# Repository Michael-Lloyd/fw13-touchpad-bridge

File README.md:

# Framework 13 Touchpad to USB bridge

Demo video can be found [here](https://youtu.be/qEcvwA03GHM?si=J2vbeN7p9iwUP8ut)

## Hardware files

You can find all of the hardware files under `hardware/` including the the gerbers, drill files and CSV that can be imported into Digikey carts. 

I've done everything in KiCAD, which is free on most systems. 

## Firmware 

The firmware is under `firmware/` and can be built using the Raspberry Pi pico-sdk toolchain. 

If you have any questions or want to talk to me about this project, you can contact me using one of the methods on my website at [micl.dev](https://micl.dev)

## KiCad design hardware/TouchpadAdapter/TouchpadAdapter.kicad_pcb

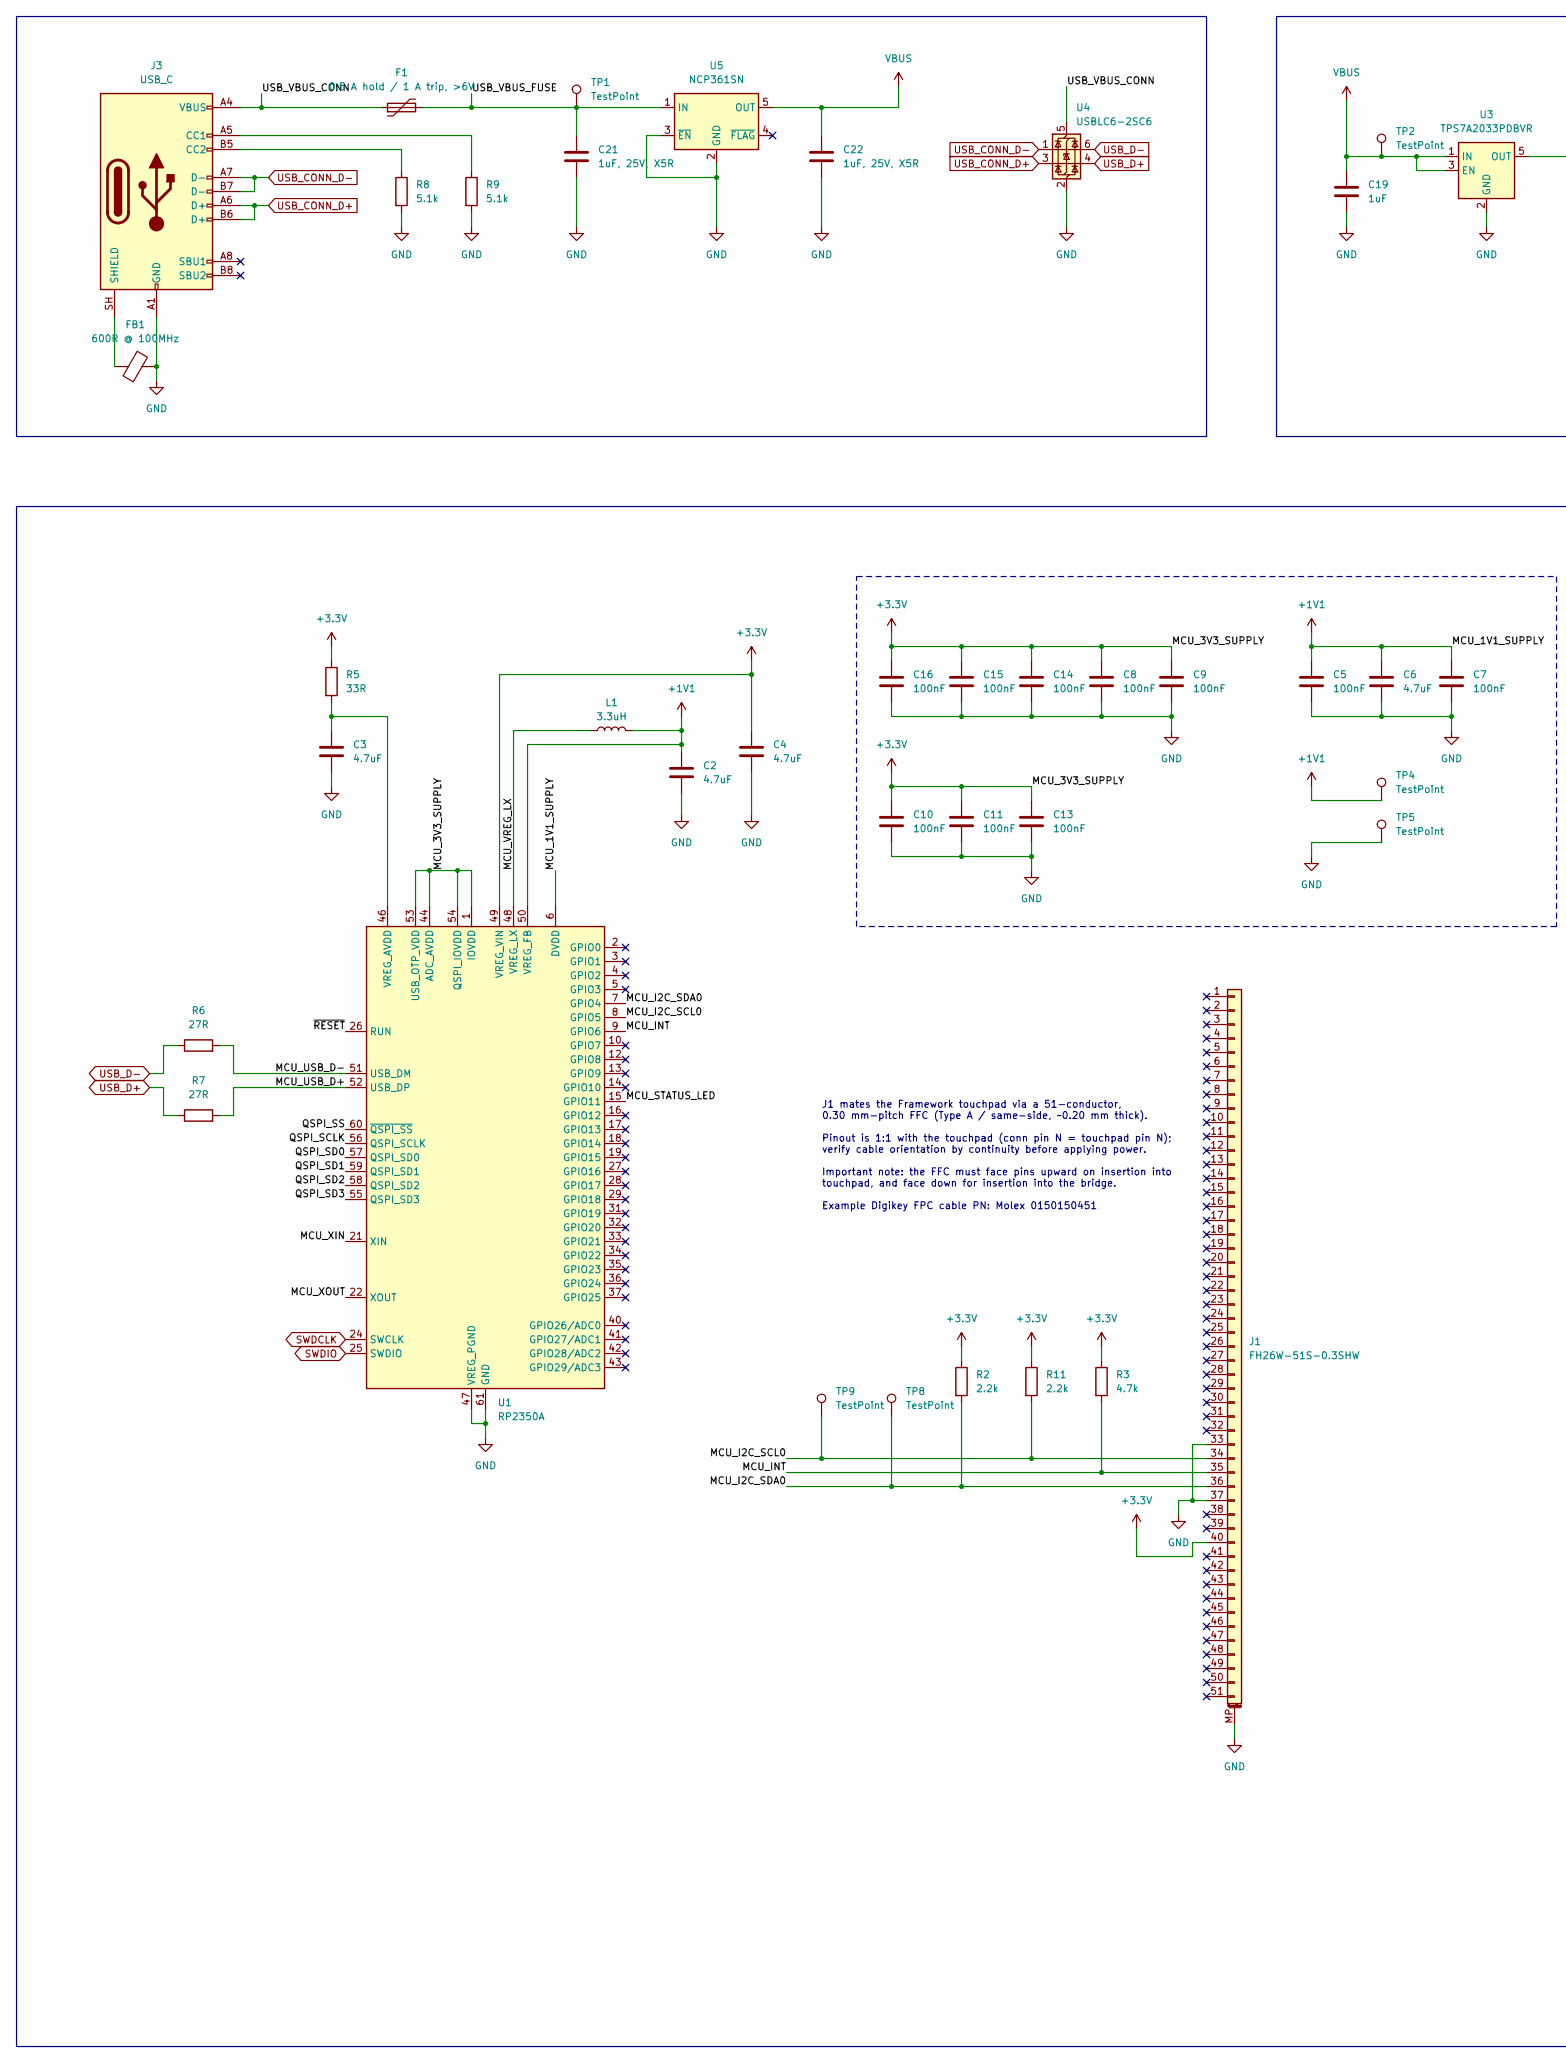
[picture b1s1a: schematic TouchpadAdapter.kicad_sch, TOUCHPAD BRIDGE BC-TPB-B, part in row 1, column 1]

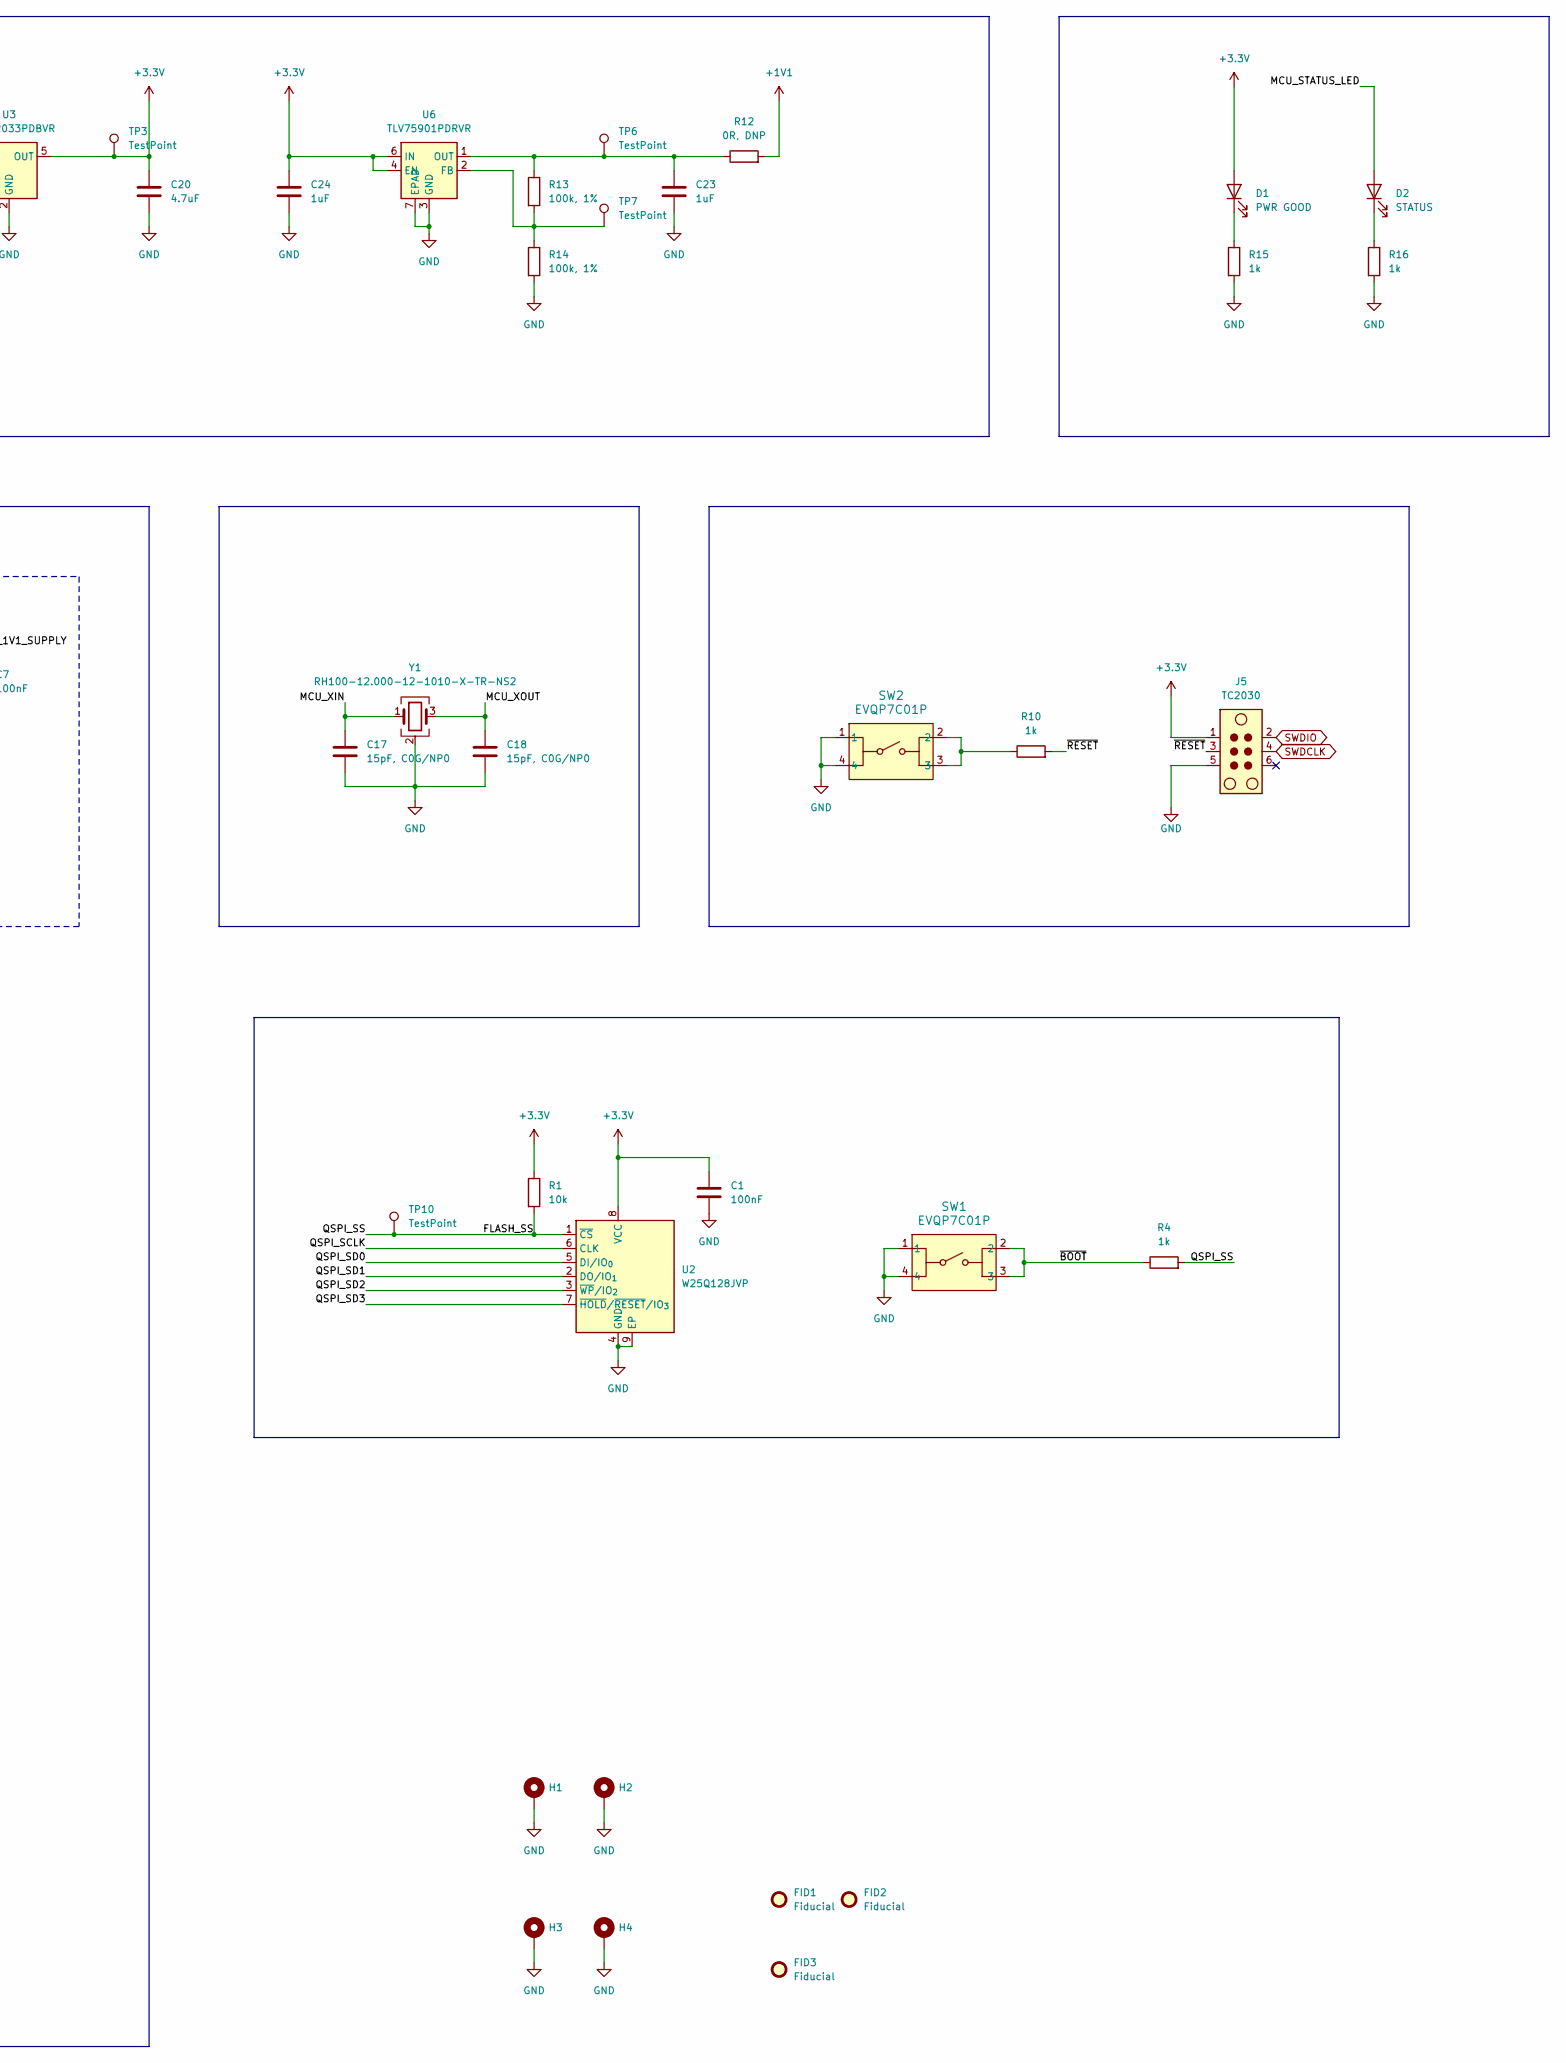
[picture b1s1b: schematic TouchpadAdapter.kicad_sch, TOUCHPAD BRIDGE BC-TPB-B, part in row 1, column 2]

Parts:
C1, C5, C7, C8, C9, C10, C11, C13, C14, C15, C16: 100nF; C_0402_1005Metric; Digikey_MPN GRM155R71E104KE14D
C2, C3, C4, C6, C20: 4.7uF; C_0603_1608Metric; Digikey_MPN GRM188Z71A475KE15J
C17, C18: 15pF, C0G/NP0; C_0402_1005Metric; Digikey_MPN GRM1555C1H150JA01D
C19, C23, C24: 1uF; C_0402_1005Metric; Digikey_MPN GRM155R61E105KA12D
C21, C22: 1uF, 25V, X5R; C_0603_1608Metric; Digikey_MPN GRT188R71E105KE13J
D1: PWR GOOD; LED_0402_1005Metric; Digikey_MPN 150040RS73220
D2: STATUS; LED_0402_1005Metric; Digikey_MPN 150040YS73220
F1: 0.5 A hold / 1 A trip, >6V; R_0603_1608Metric; Digikey_MPN 0603L050SLYR
FB1: 600R @ 100MHz; R_0402_1005Metric; Digikey_MPN BLM15HD601SN1D
FID1, FID2, FID3: Fiducial; Fiducial_1mm_Mask2mm
H1, H2, H3, H4: MountingHole_Pad; MountingHole_2.2mm_M2_Pad
J1: FH26W-51S-0.3SHW; FH26W-51S-0.3SHW60; Digikey_MPN FH26W-51S-0.3SHW(60)
J3: USB_C; USB_C_Receptacle_GCT_USB4105-xx-A_16P_TopMnt_Horizontal
J5: TC2030; Tag-Connect_TC2030-IDC-NL_2x03_P1.27mm_Vertical; Digikey_MPN TC2030-IDC-NL
L1: 3.3uH; L_1008_2520Metric; Digikey_MPN TFM252012ALVA3R3MTAA
R1: 10k; R_0402_1005Metric; Digikey_MPN ERJ-2RKF1002X
R2, R11: 2.2k; R_0402_1005Metric; Digikey_MPN ERJ-2RKF2201X
R3: 4.7k; R_0402_1005Metric; Digikey_MPN ERJ-2RKF4701X
R4, R10, R15, R16: 1k; R_0402_1005Metric; Digikey_MPN ERJ-2RKF1001X
R5: 33R; R_0402_1005Metric; Digikey_MPN ERJ-2RKF33R0X
R6, R7: 27R; R_0402_1005Metric; Digikey_MPN ERJ-2RKF27R0X
R8, R9: 5.1k; R_0402_1005Metric; Digikey_MPN ERJ-2RKF5101X
R12: 0R, DNP; R_0402_1005Metric; Digikey_MPN ERJ-2GE0R00X
R13, R14: 100k, 1%; R_0402_1005Metric; Digikey_MPN CRCW0402100KFKED
SW1, SW2: EVQP7C01P; Digikey_MPN EVQ-P7C01P
TP1, TP2, TP3, TP4, TP5, TP6, TP7, TP8, TP9, TP10: TestPoint; TestPoint_Pad_D0.5mm
U1: RP2350A; QFN-60-1EP_7x7mm_P0.4mm_EP3.4x3.4mm; Digikey_MPN RP2350A
U2: W25Q128JVP; WSON-8-1EP_6x5mm_P1.27mm_EP3.4x4.3mm; Digikey_MPN W25Q128JVPIQ
U3: TPS7A2033PDBVR; SOT-23-5; Digikey_MPN TPS7A2033PDBVR
U4: USBLC6-2SC6; SOT-23-6; Digikey_MPN USBLC6-2SC6Y
U5: NCP361SN; TSOP-5_1.65x3.05mm_P0.95mm; Digikey_MPN NCP361SNT1G
U6: TLV75901PDRVR; WSON-6-1EP_2x2mm_P0.65mm_EP1x1.6mm; Digikey_MPN TLV75901PDRVR
Y1: RH100-12.000-12-1010-X-TR-NS2; Crystal_SMD_3225-4Pin_3.2x2.5mm; Digikey_MPN RH100-12.000-12-1010-X-TR-NS2

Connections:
+1V1: C2.1, C5.1, C6.1, C7.1, L1.2, R12.2, TP4.1 (1_1), U1.6 (DVDD), U1.23 (DVDD), U1.39 (DVDD), U1.50 (VREG_FB)
+3.3V: C1.1, C4.1, C8.1, C9.1, C10.1, C11.1, C13.1, C14.1, C15.1, C16.1, C20.1, C24.1, D1.2 (A), J1.40, J5.1, R1.1, R2.1, R3.1, R5.1, R11.1, TP3.1 (1_1), U1.1 (IOVDD), U1.11 (IOVDD), U1.20 (IOVDD), U1.30 (IOVDD), U1.38 (IOVDD), U1.44 (ADC_AVDD), U1.45 (IOVDD), U1.49 (VREG_VIN), U1.53 (USB_OTP_VDD), U1.54 (QSPI_IOVDD), U2.8 (VCC), U3.5 (OUT), U6.4 (EN), U6.6 (IN)
/FLASH_SS: R1.2, R4.2, TP10.1 (1_1), U1.60 (~QSPI_SS), U2.1 (~CS)
/MCU_I2C_SCL0: J1.34, R11.2, TP9.1 (1_1), U1.8 (GPIO5)
/MCU_I2C_SDA0: J1.36, R2.2, TP8.1 (1_1), U1.7 (GPIO4)
/MCU_INT: J1.35, R3.2, U1.9 (GPIO6)
/MCU_STATUS_LED: D2.2 (A), U1.15 (GPIO11)
/MCU_USB_D+: R7.2, U1.52 (USB_DP)
/MCU_USB_D-: R6.2, U1.51 (USB_DM)
/MCU_VREG_LX: L1.1, U1.48 (VREG_LX)
/MCU_XIN: C17.1, U1.21 (XIN), Y1.1
/MCU_XOUT: C18.1, U1.22 (XOUT), Y1.3
/QSPI_SCLK: U1.56 (QSPI_SCLK), U2.6 (CLK)
/QSPI_SD0: U1.57 (QSPI_SD0), U2.5 (DI/IO_{0})
/QSPI_SD1: U1.59 (QSPI_SD1), U2.2 (DO/IO_{1})
/QSPI_SD2: U1.58 (QSPI_SD2), U2.3 (~WP/IO_{2})
/QSPI_SD3: U1.55 (QSPI_SD3), U2.7 (~HOLD/~RESET/IO_{3})
/USB_VBUS_CONN: F1.1, J3.A4 (VBUS), J3.A9 (VBUS), J3.B4 (VBUS), J3.B9 (VBUS), U4.5 (VBUS)
/USB_VBUS_FUSE: C21.1, F1.2, TP1.1 (1_1), U5.1 (IN)
/~BOOT: R4.1, SW1.2, SW1.3
/~RESET: J5.3, R10.2, U1.26 (RUN)
GND: C1.2, C2.2, C3.2, C4.2, C5.2, C6.2, C7.2, C8.2, C9.2, C10.2, C11.2, C13.2, C14.2, C15.2, C16.2, C17.2, C18.2, C19.2, C20.2, C21.2, C22.2, C23.2, C24.2, FB1.2, H1.1 (1_1), H2.1 (1_1), H3.1 (1_1), H4.1 (1_1), J1.33, J1.37, J1.MP (MountPin), J3.A1 (GND), J3.A12 (GND), J3.B1 (GND), J3.B12 (GND), J5.5, R8.2, R9.2, R14.2, R15.2, R16.2, SW1.1, SW1.4, SW2.1, SW2.4, TP5.1 (1_1), U1.47 (VREG_PGND), U1.61 (GND), U2.4 (GND), U2.9 (EP), U3.2 (GND), U4.2 (GND), U5.2 (GND), U5.3 (~EN), U6.3 (GND), U6.7 (EPAD), Y1.2 (G), Y1.4 (G)
unnamed: D1.1 (K), R15.1
unnamed: D2.1 (K), R16.1
unnamed: J3.A5 (CC1), R9.1
unnamed: J3.B5 (CC2), R8.1
unnamed: FB1.1, J3.SH (SHIELD)
unnamed: R10.1, SW2.2, SW2.3
unnamed: C3.1, R5.2, U1.46 (VREG_AVDD)
unnamed: R13.2, R14.1, TP7.1 (1_1), U6.2 (FB)
unnamed: C23.1, R12.1, R13.1, TP6.1 (1_1), U6.1 (OUT)
SWDCLK: J5.4, U1.24 (SWCLK)
SWDIO: J5.2, U1.25 (SWDIO)
USB_CONN_D+: J3.A6 (D+), J3.B6 (D+), U4.3 (I/O2)
USB_CONN_D-: J3.A7 (D-), J3.B7 (D-), U4.1 (I/O1)
USB_D+: R7.1, U4.4 (I/O2)
USB_D-: R6.1, U4.6 (I/O1)
VBUS: C19.1, C22.1, TP2.1 (1_1), U3.1 (IN), U3.3 (EN), U5.5 (OUT)

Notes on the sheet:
J1 mates the Framework touchpad via a 51-conductor, 0.30 mm-pitch FFC (Type A / same-side, ~0.20 mm thick). Pinout is 1:1 with the touchpad (conn pin N = touchpad pin N); verify cable orientation by continuity before applying power. Important note: the FFC must face pins upward on insertion into to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

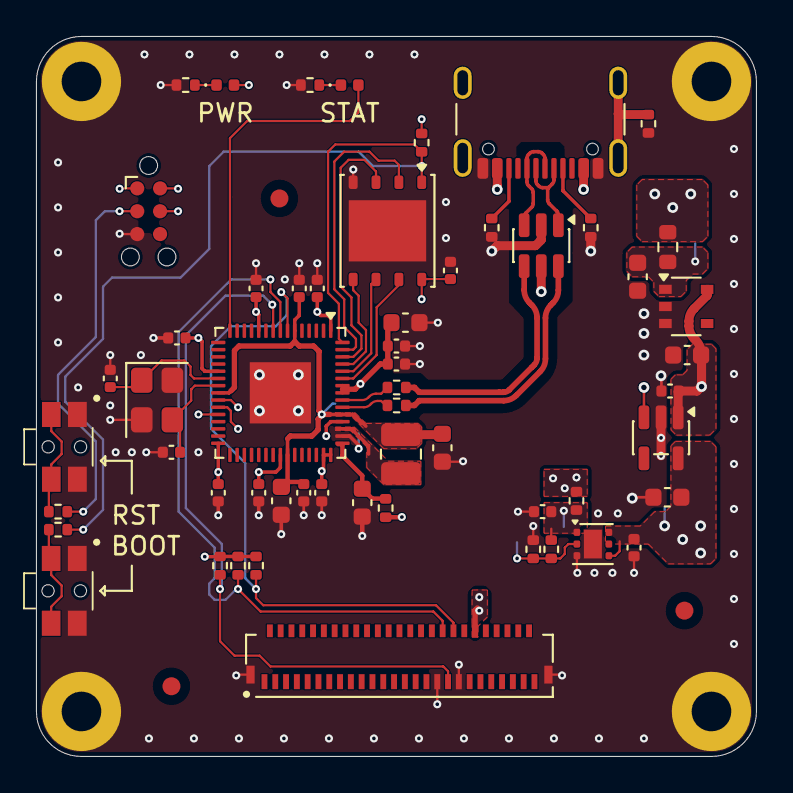
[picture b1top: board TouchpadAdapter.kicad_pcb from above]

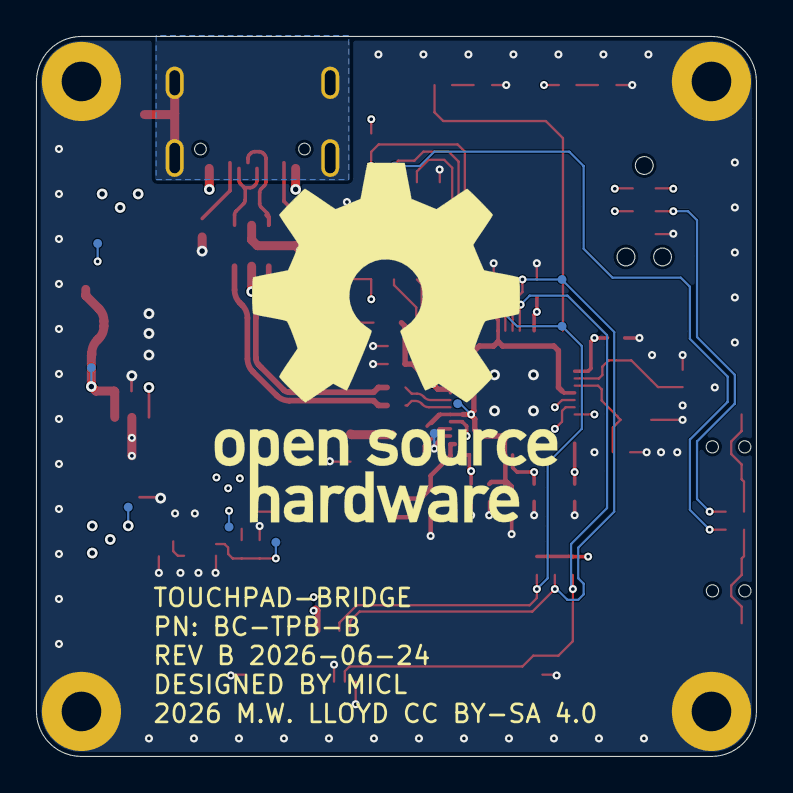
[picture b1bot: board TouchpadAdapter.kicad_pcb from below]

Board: 4 copper layers, 40.0 x 40.0 mm, 73 parts (10 on the bottom side), 38 nets.

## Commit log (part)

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2026-06-23 Initial rev b files
2026-06-23 Firmware and repository release

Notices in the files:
hardware/TouchpadAdapter/TouchpadAdapter.kicad_pcb:
2026 M.W. LLOYD CC BY-SA 4.0
